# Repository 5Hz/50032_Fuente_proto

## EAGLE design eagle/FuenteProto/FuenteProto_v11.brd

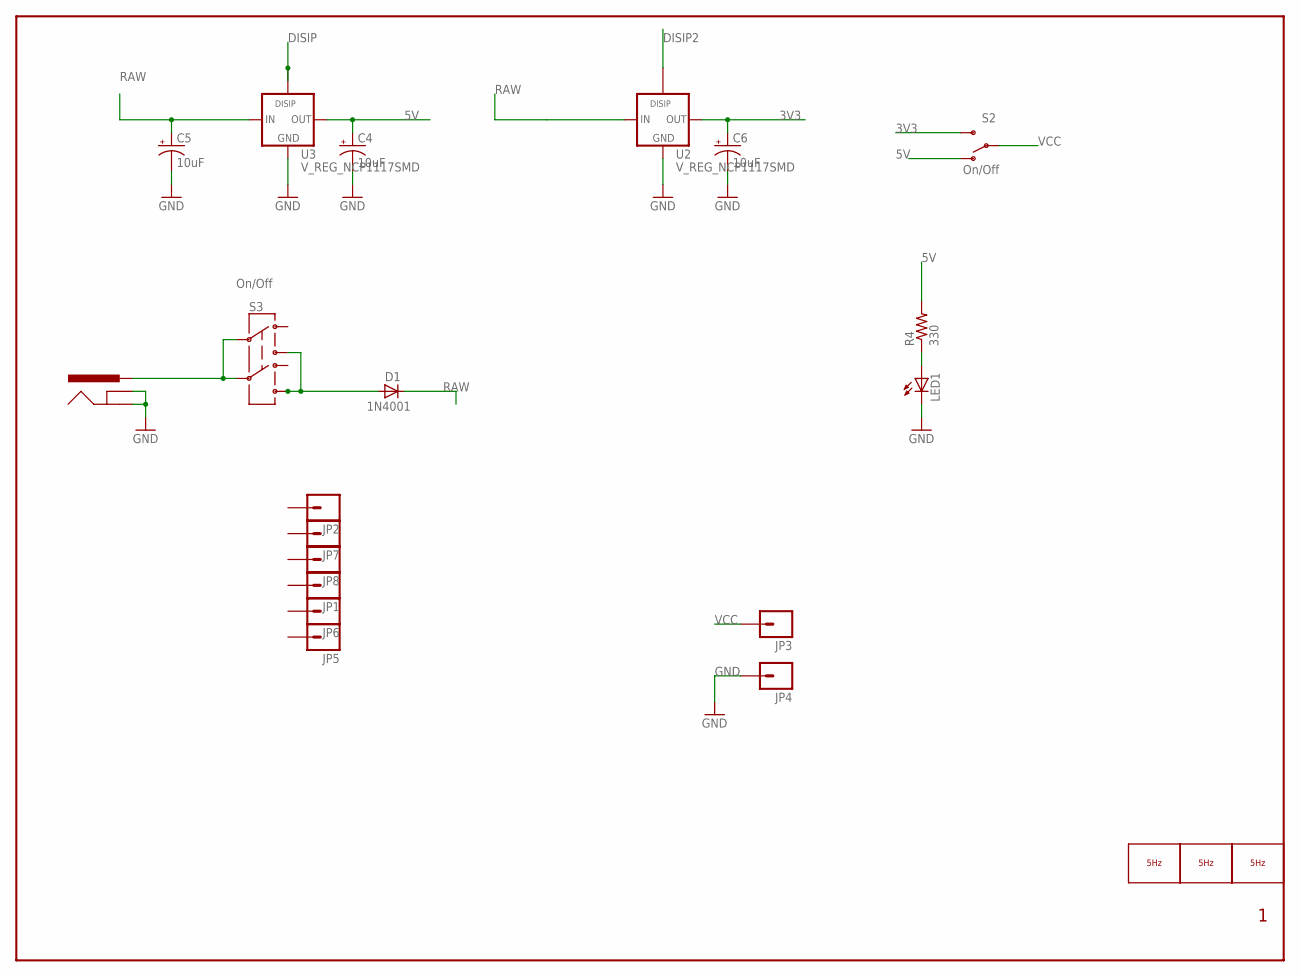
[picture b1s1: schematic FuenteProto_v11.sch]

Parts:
C4, C5, C6: 10uF; EIA3216
D1: 1N4001; SMA-DIODE
J1: POWER_JACKPTH; POWER_JACK_PTH
JP1, JP2, JP3, JP4, JP5, JP6, JP7, JP8: M01PTH; 1X01
LED1: LED0603; LED-0603
LOGO1: LOGO_5HZ_CIRC_3.5MM; 5HZ_LOGO_CIRC_3.5MM
LOGO2: LOGO_5HZ_WEB_10MM; 5HZ_WEB_10MM
LOGO3: LOGO_5HZ_H_10MM; 5HZ_LOGO_H_10MM
R4: 330; 0603
S2, S3: On/Off; AYZ0202
U2, U3: V_REG_NCP1117SMD; SOT223

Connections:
3V3: C6.A (+), S2.3 (S), U2.2 (OUT)
5V: C4.A (+), R4.2, S2.1 (O), U3.2 (OUT)
DISIP: U3.4
DISIP2: U2.4
GND: C4.C (-), C5.C (-), C6.C (-), J1.GND, J1.GNDBREAK, JP4.1, LED1.C, U2.1 (GND), U3.1 (GND)
unnamed: D1.A, S3.1 (3), S3.4 (6)
unnamed: J1.PWR, S3.2, S3.5
unnamed: LED1.A, R4.1
RAW: C5.A (+), D1.C, U2.3 (IN), U3.3 (IN)
VCC: JP3.1, S2.2

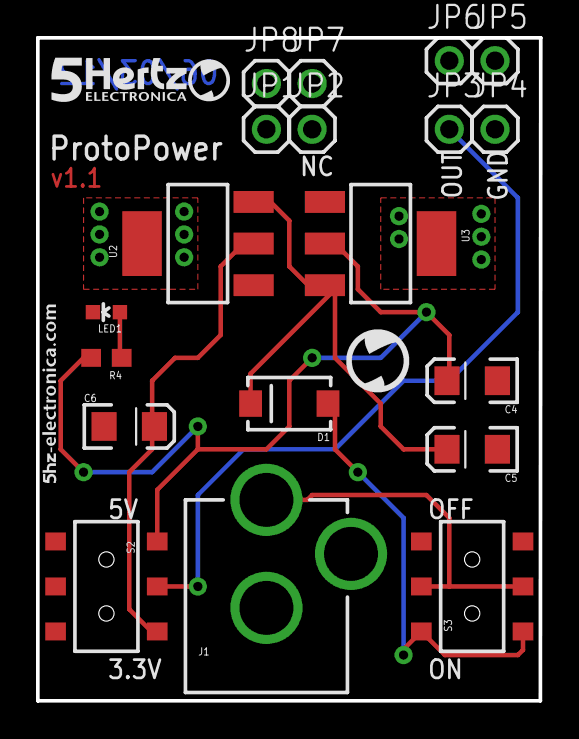
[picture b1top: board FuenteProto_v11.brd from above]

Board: 2 copper layers, 27.9 x 36.8 mm, 22 parts (0 on the bottom side), 8 nets.

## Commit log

2014-01-10 creación
